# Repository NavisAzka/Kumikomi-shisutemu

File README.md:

<div align="center">
  
  <br><br>

  <p>
    <b>Praktikum ini merupakan bagian dari mata kuliah Mikrokontroler & Embedded System yang bertujuan untuk memberikan pemahaman praktis mengenai pemrograman mikrokontroler, interfacing sensor/aktuator, komunikasi serial, real-time system, hingga dasar sistem kontrol.</b>
  </p>

  <p>

  </p>
</div>

---

## 📚 Apa yang Akan Dipelajari?

Dalam modul-modul praktikum ini, kamu akan mempelajari dan mengimplementasikan beberapa konsep penting, di antaranya:

### 1. **Pengantar Mikrokontroler & Dasar Pemrograman**

- Instalasi dan konfigurasi PlatformIO di VSCode
- Pengenalan STM32 Blackpill (framework Arduino) dan ESP32 (framework ESP-IDF & Arduino)
- Pull-up dan pull-down resistor (eksternal maupun internal) pada input tombol
- Debouncing input tombol berbasis GPIO
- Level shifter sebagai konverter level tegangan logika (3.3V ↔ 5V)

### 2. **Sensor Berdasarkan Basis Pengukuran & Aktuator Motor**

- Sensor resistif (LDR), kapasitif (touch sensor TTP223), dan induktif (hall effect)
- Sensor basis lain: akustik (ultrasonik HC-SR04) dan optik (IR obstacle)
- Kontrol kecepatan motor DC menggunakan PWM
- Kontrol motor stepper dan motor servo

### 3. **Komunikasi Serial & Interfacing Modul**

- Komunikasi UART antar board ESP32
- Komunikasi I2C (master-slave antar board, serta multi-device pada satu bus: OLED + IMU)
- Komunikasi SPI antar board maupun ke modul sensor eksternal (IMU MPU6500)
- DMA untuk transfer data SPI secara *burst*

### 4. **Interrupt, Timer, Watchdog, & Multitasking**

- External interrupt untuk manual recovery dan decoding quadrature encoder
- Timer interrupt untuk tugas periodik non-blocking
- Watchdog timer untuk menjaga keandalan sistem
- Multitasking menggunakan FreeRTOS (task & queue)

### 5. **Pemrosesan Data Sensor & Dasar Sistem Kontrol (Filtering & PID)**

- Konversi pulsa encoder menjadi RPM
- Filtering sinyal: low-pass filter alpha dan Kalman filter
- Sistem kontrol closed-loop: on-off dan Proportional (P)
- Kontrol PID lengkap beserta tuning parameter

---

## 🛠 Aplikasi dan Tools yang Dibutuhkan

Apa aja sih aplikasi yang kalian butuhkan?
Nah, untuk melakukan praktikum ini, kamu perlu menginstal aplikasi berikut:

- **Visual Studio Code**
  Editor kode utama yang digunakan sepanjang praktikum.
  Link Download : https://code.visualstudio.com/
- **PlatformIO IDE** (ekstensi VSCode)
  Lingkungan pengembangan embedded untuk membuat, build, dan upload project ke STM32 maupun ESP32.
  Instalasi lengkap ada di [setup_vscode_platformio.md](setup_vscode_platformio.md)
- **Driver USB-to-Serial**
  ST-Link (STSW-LINK009) untuk STM32 Blackpill, dan CP2102/CH340 untuk board ESP32 DevKit.
- **Serial Plotter** (ekstensi VSCode oleh badlogic)
  Dibutuhkan pada Modul 5 untuk memvisualisasikan data filtering & PID secara real-time, karena VSCode tidak memiliki Serial Plotter bawaan seperti Arduino IDE.
  Repository: https://github.com/badlogic/serial-plotter

---

## Bagaimana cara membaca modul dan buat laporannya??

Setiap modul disusun sebagai file Markdown terpisah (`Modul_1` s.d. `Modul_5`), masing-masing berisi capaian pembelajaran, alat & bahan, dasar teori, langkah kerja tiap percobaan (lengkap dengan skema rangkaian, `platformio.ini`, dan kode program), hingga tugas akhir modul. Kamu bisa membuka modul yang ingin dipelajari langsung dari folder ini, atau men-download/meng-clone seluruh repository ini agar dapat membuka semua modul secara offline.

Sebelum memulai Modul 1, pastikan langkah-langkah pada [setup_vscode_platformio.md](setup_vscode_platformio.md) sudah selesai dilakukan.

Format laporan dan rubrik penilaian disesuaikan oleh dosen/asisten pengampu masing-masing kelas.

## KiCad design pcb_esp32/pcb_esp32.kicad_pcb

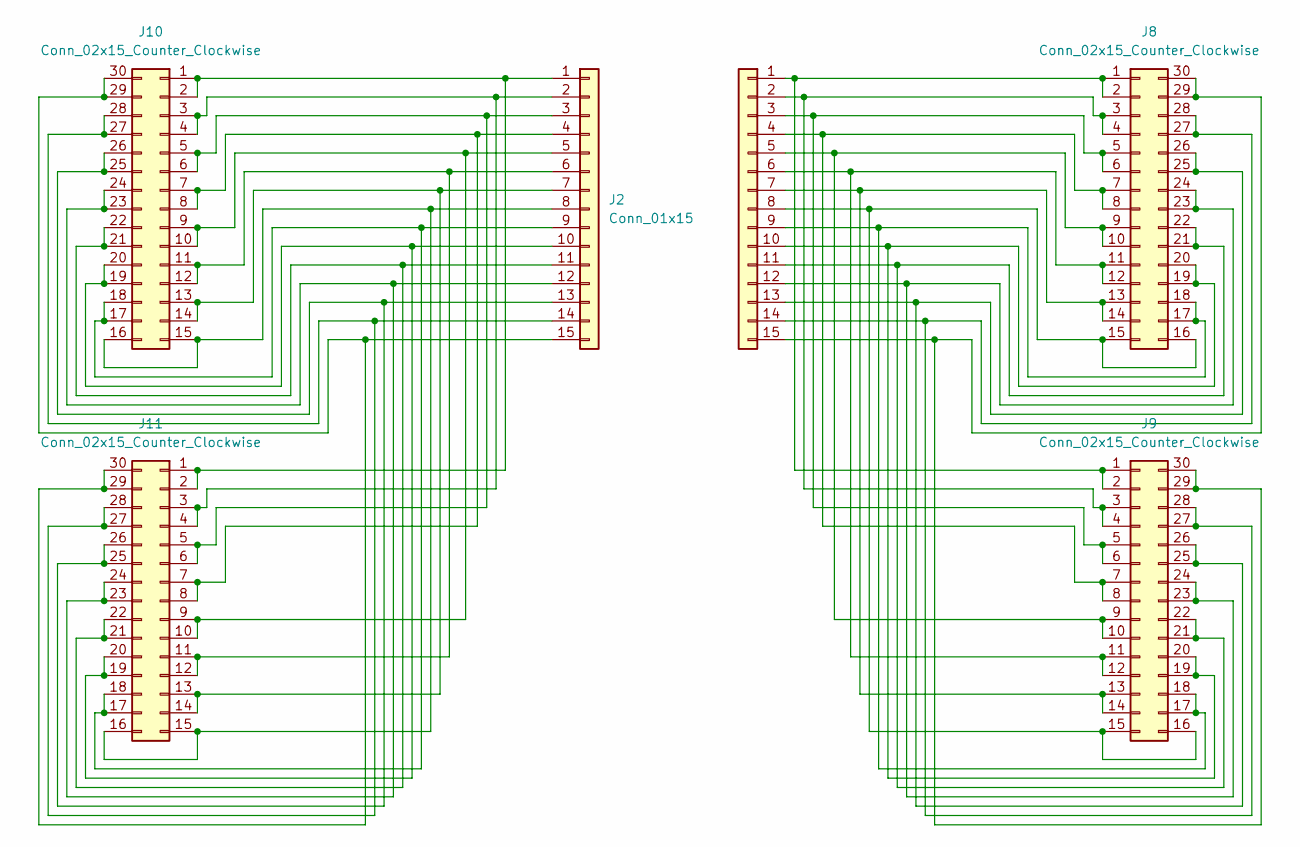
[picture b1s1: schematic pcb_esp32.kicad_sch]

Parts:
J1, J2: Conn_01x15; PinSocket_1x15_P2.54mm_Vertical
J8, J9, J10, J11: Conn_02x15_Counter_Clockwise; PinSocket_2x15_P2.54mm_Vertical

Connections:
unnamed: J1.1, J8.1, J8.2, J9.1, J9.2
unnamed: J1.2, J8.3, J8.4, J9.3, J9.4
unnamed: J1.3, J8.5, J8.6, J9.5, J9.6
unnamed: J1.4, J8.7, J8.8, J9.7, J9.8
unnamed: J1.5, J8.9, J8.10, J9.9, J9.10
unnamed: J1.6, J8.11, J8.12, J9.11, J9.12
unnamed: J1.7, J8.13, J8.14, J9.13, J9.14
unnamed: J1.8, J8.15, J8.16, J9.15, J9.16
unnamed: J1.9, J8.17, J8.18, J9.17, J9.18
unnamed: J1.10, J8.19, J8.20, J9.19, J9.20
unnamed: J1.11, J8.21, J8.22, J9.21, J9.22
unnamed: J1.12, J8.23, J8.24, J9.23, J9.24
unnamed: J1.13, J8.25, J8.26, J9.25, J9.26
unnamed: J1.14, J8.27, J8.28, J9.27, J9.28
unnamed: J1.15, J8.29, J8.30, J9.29, J9.30
unnamed: J2.1, J10.1, J10.2, J11.1, J11.2
unnamed: J2.2, J10.3, J10.4, J11.3, J11.4
unnamed: J2.3, J10.5, J10.6, J11.5, J11.6
unnamed: J2.4, J10.7, J10.8, J11.7, J11.8
unnamed: J2.5, J10.9, J10.10, J11.9, J11.10
unnamed: J2.6, J10.11, J10.12, J11.11, J11.12
unnamed: J2.7, J10.13, J10.14, J11.13, J11.14
unnamed: J2.8, J10.15, J10.16, J11.15, J11.16
unnamed: J2.9, J10.17, J10.18, J11.17, J11.18
unnamed: J2.10, J10.19, J10.20, J11.19, J11.20
unnamed: J2.11, J10.21, J10.22, J11.21, J11.22
unnamed: J2.12, J10.23, J10.24, J11.23, J11.24
unnamed: J2.13, J10.25, J10.26, J11.25, J11.26
unnamed: J2.14, J10.27, J10.28, J11.27, J11.28
unnamed: J2.15, J10.29, J10.30, J11.29, J11.30

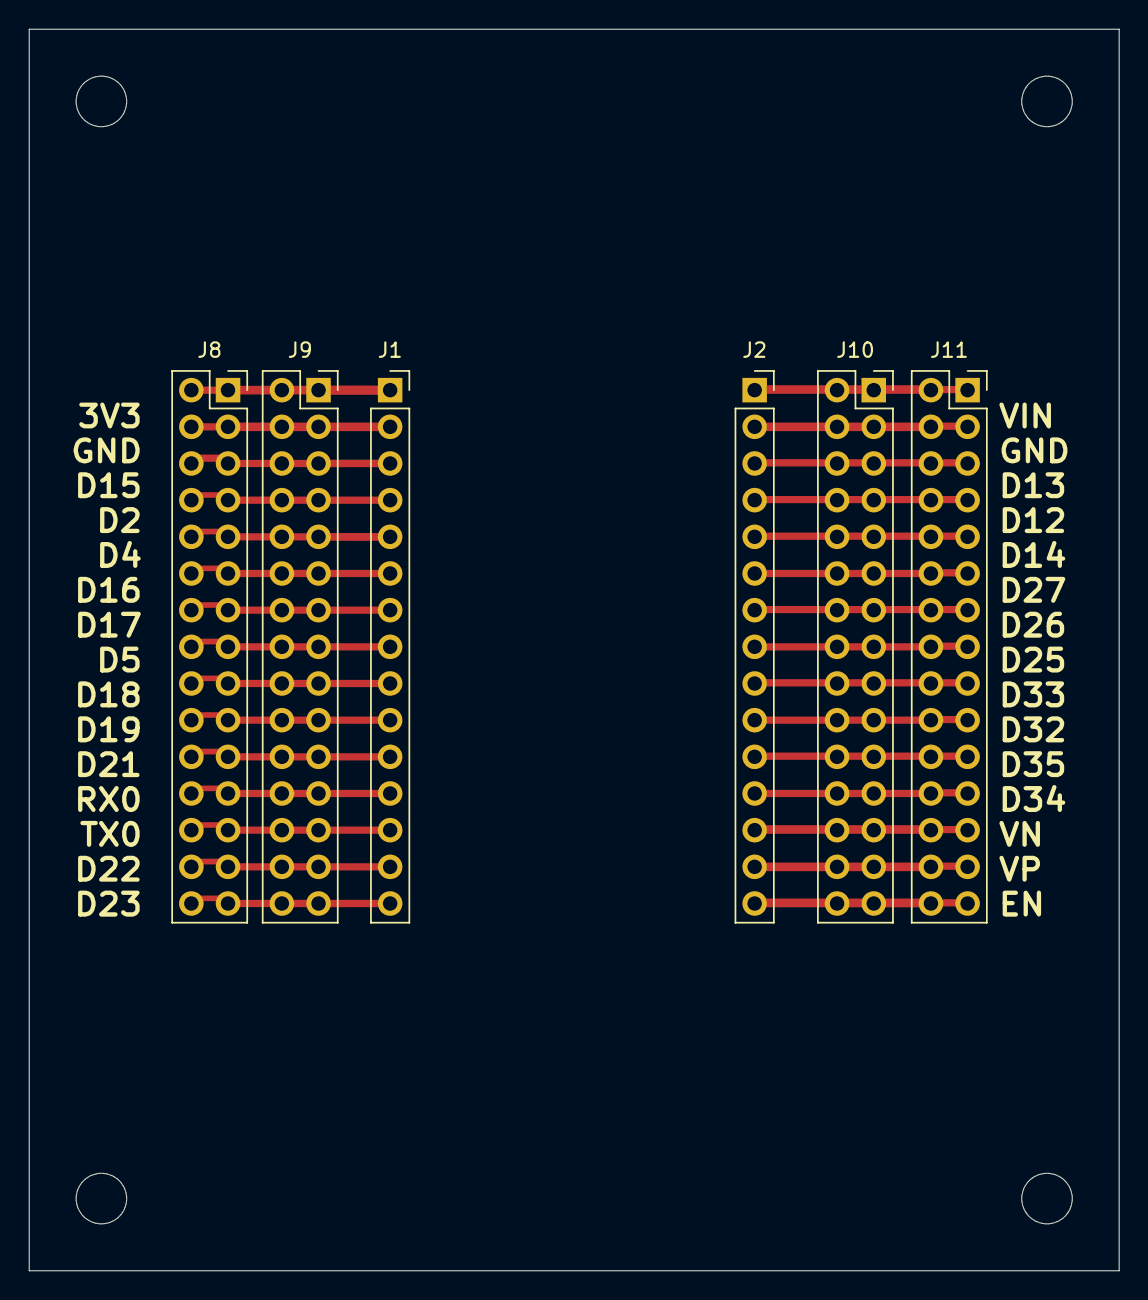
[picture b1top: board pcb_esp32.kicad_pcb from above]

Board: 2 copper layers, 75.5 x 86.0 mm, 6 parts (0 on the bottom side), 30 nets.
